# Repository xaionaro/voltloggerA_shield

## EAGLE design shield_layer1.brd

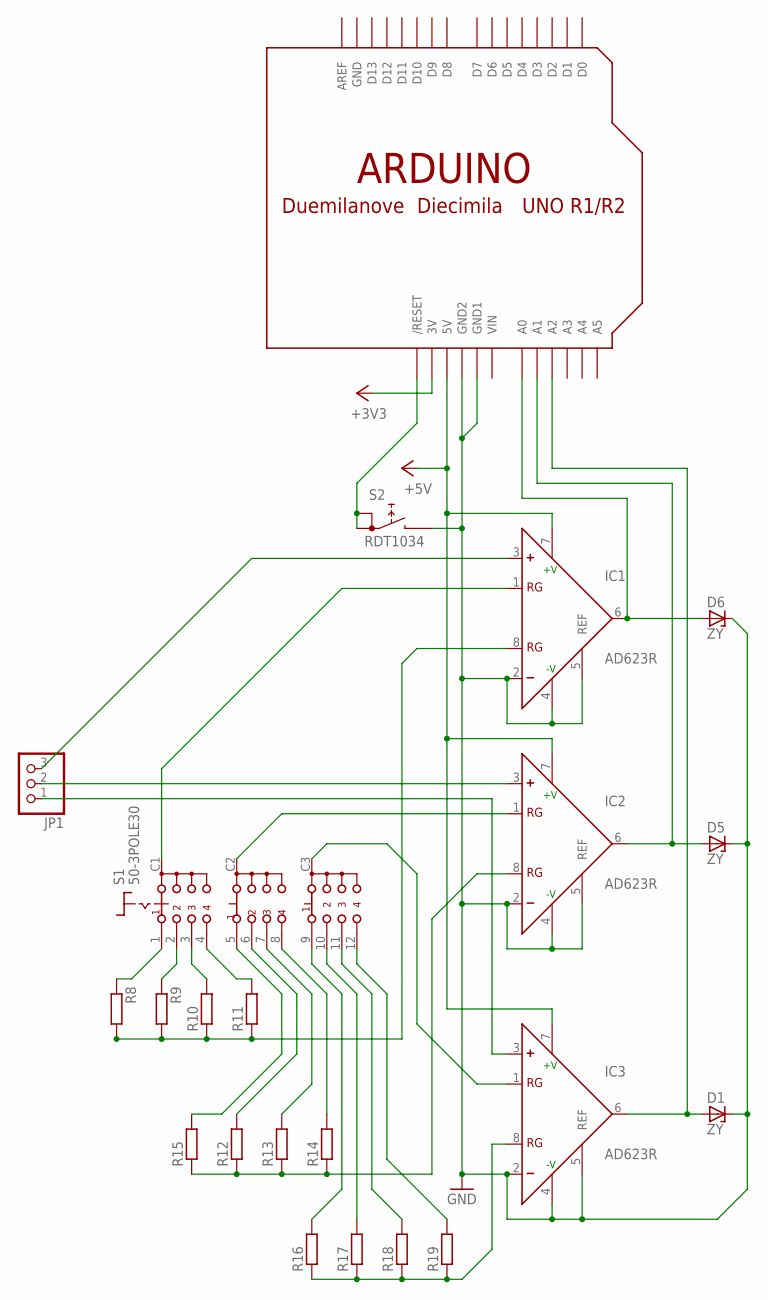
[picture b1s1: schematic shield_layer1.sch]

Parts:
D1, D5, D6: ZY; P1Z12
IC1, IC2, IC3: AD623R; SO8
JP1: PINHD-1X3; 1X03
R8, R9, R10, R11, R12, R13, R14, R15, R16, R17, R18, R19: R-EU_0207/10; 0207/10
S1: 50-3POLE30
S2: RDT1034
U$1: ARDUINOUNO; ARDUINO

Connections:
5V: U$1.3V
+5V: IC1.7 (+V), IC2.7 (+V), IC3.7 (+V), U$1.5V
GND: D1.C, D5.C, D6.C, IC1.2 (-), IC1.4 (-V), IC1.5 (REF), IC2.2 (-), IC2.4 (-V), IC2.5 (REF), IC3.2 (-), IC3.4 (-V), IC3.5 (REF), S2.B, U$1.GND, U$1.GND1, U$1.GND2
unnamed: IC1.1 (RG), S1.C1 (A)
unnamed: IC2.1 (RG), S1.C2 (B)
unnamed: IC2.8 (RG), R12.1, R13.1, R14.1, R15.1
unnamed: IC3.1 (RG), S1.C3 (C)
unnamed: IC3.8 (RG), R16.1, R17.1, R18.1, R19.1
unnamed: D6.A, IC1.6 (OUT), U$1.A0
unnamed: D5.A, IC2.6 (OUT), U$1.A1
unnamed: D1.A, IC3.6 (OUT), U$1.A2
unnamed: R8.1, S1.1 (A1)
unnamed: R9.1, S1.2 (A2)
unnamed: R10.2, S1.3 (A3)
unnamed: S2.A, S2.A1, U$1.RESET (/RESET)
unnamed: R11.2, S1.4 (A4)
unnamed: R15.2, S1.5 (B1)
unnamed: R12.2, S1.6 (B2)
unnamed: R13.2, S1.7 (B3)
unnamed: R14.2, S1.8 (B4)
unnamed: R16.2, S1.9 (C1)
unnamed: R17.2, S1.10 (C2)
unnamed: R18.2, S1.11 (C3)
unnamed: R19.2, S1.12 (C4)
unnamed: IC1.8 (RG), R8.2, R9.2, R10.1, R11.1
unnamed: IC1.3 (+), JP1.3
unnamed: IC3.3 (+), JP1.1
unnamed: IC2.3 (+), JP1.2
VIN: U$1.VIN

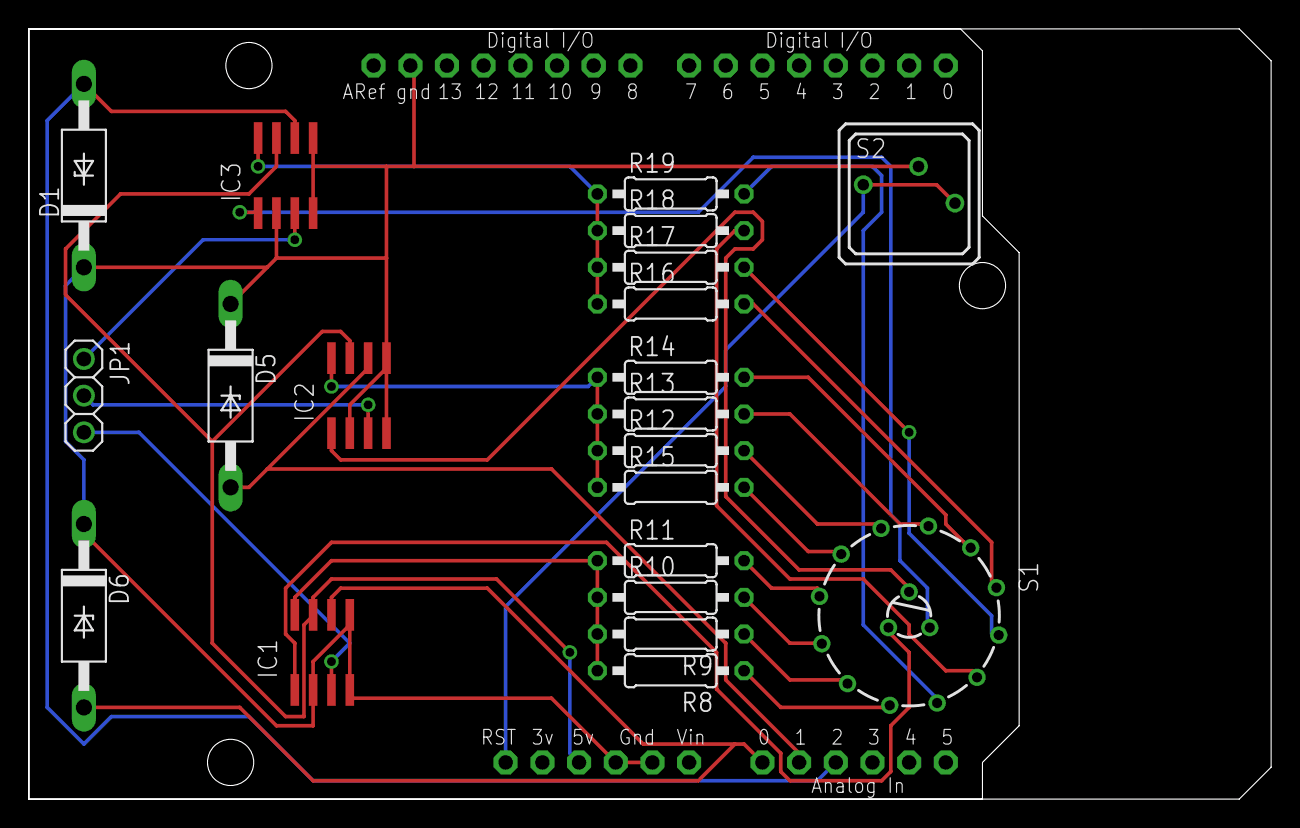
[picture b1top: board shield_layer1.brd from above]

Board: 2 copper layers, 86.0 x 53.3 mm, 22 parts (0 on the bottom side), 27 nets.

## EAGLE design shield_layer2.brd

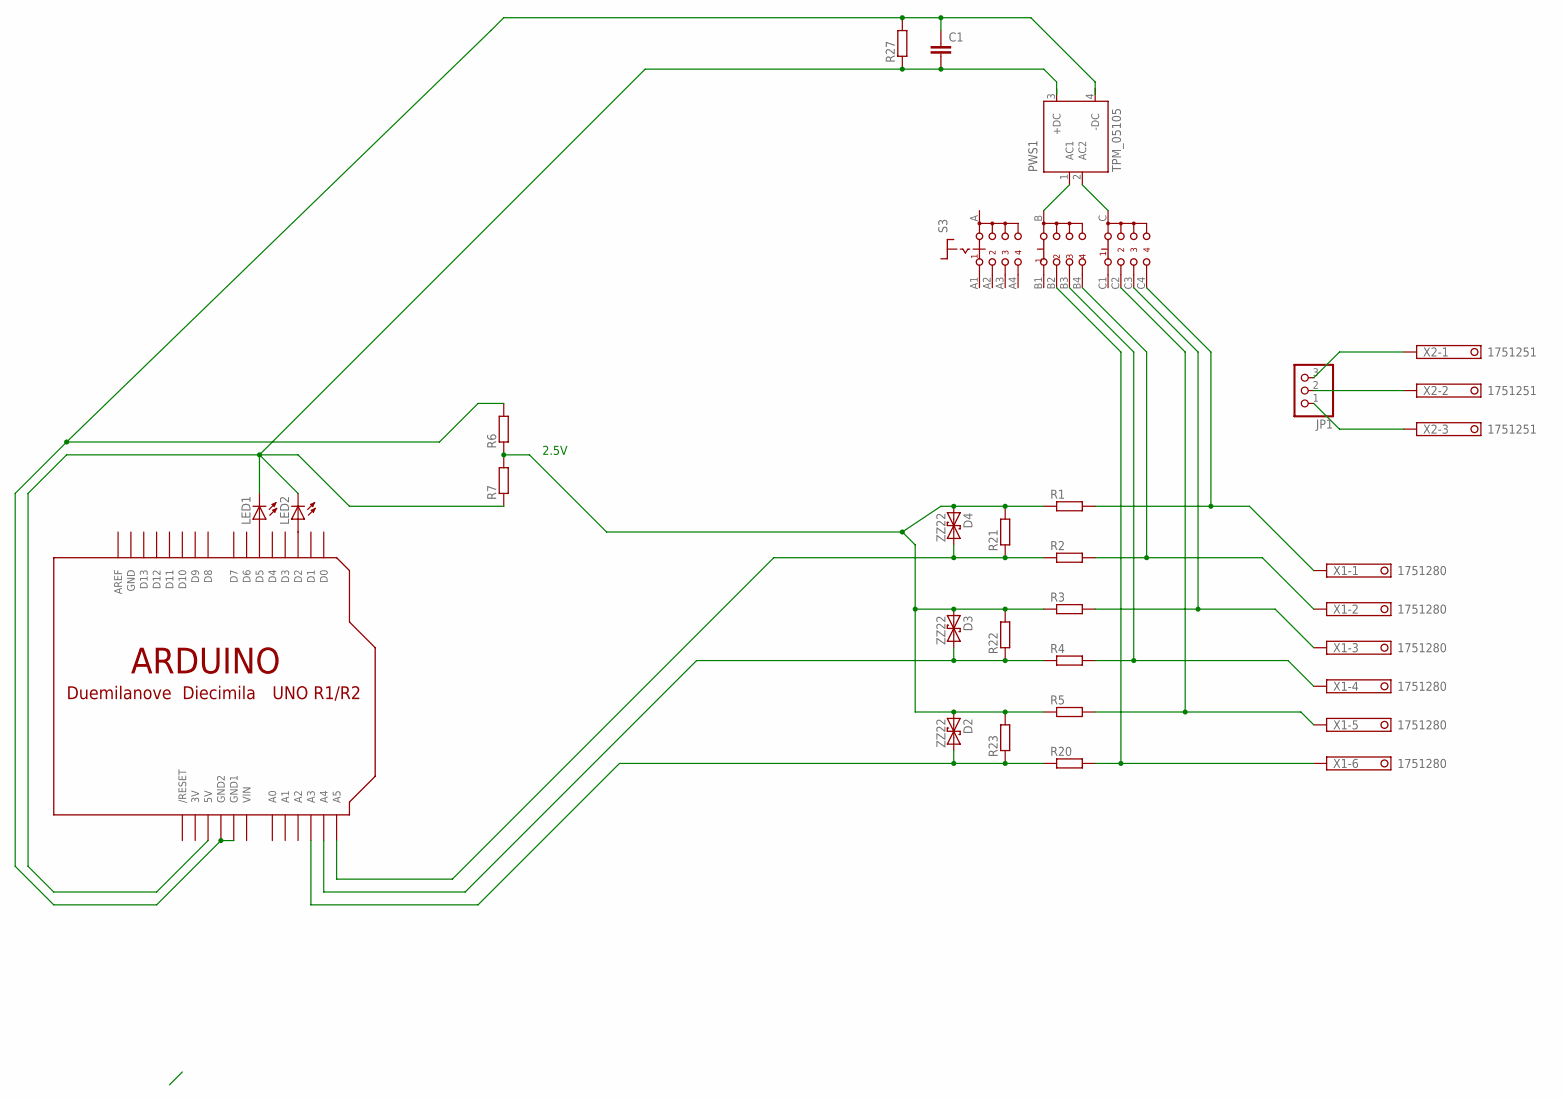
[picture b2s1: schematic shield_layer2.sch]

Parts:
C1: C-EU050-045X075; C050-045X075
D2, D3, D4: ZZ22; P2-15
JP1: PINHD-1X3CB; 1X03-CLEANBIG
LED1, LED2: LED5MM
PWS1: TPM_05105; 05105
R1, R2, R3, R4, R5, R20: R-EU_0617/22; 0617/22
R6, R7, R21, R22, R23, R27: R-EU_0207/10; 0207/10
S3: CK103X04
U$1: ARDUINOUNO; ARDUINO
X1: 1751280
X2: 1751251

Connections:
3V: U$1.3V
GND: U$1.GND
unnamed: C1.2, LED1.K (C), LED2.K (C), R7.1, R27.1, U$1.5V
unnamed: PWS1.1 (AC1), S3.B
unnamed: JP1.3, X2.1
unnamed: JP1.2, X2.2
unnamed: JP1.1, X2.3
unnamed: PWS1.2 (AC2), S3.C
unnamed: D2.C (2), R20.1, R23.1, U$1.A3
unnamed: D3.C (2), R4.1, R22.1, U$1.A4
unnamed: D4.C (2), R2.1, R21.1, U$1.A5
unnamed: C1.1, R6.2, R27.2, U$1.GND1, U$1.GND2
unnamed: LED2.A, U$1.D2
unnamed: LED1.A, U$1.D5
unnamed: R1.2, S3.C4, X1.1
unnamed: R3.2, S3.C3, X1.3
unnamed: D2.A (1), D3.A (1), D4.A (1), R1.1, R3.1, R5.1, R6.1, R7.2, R21.2, R22.2, R23.2
unnamed: R5.2, S3.C2, X1.5
unnamed: R20.2, S3.B2, X1.6
unnamed: R2.2, S3.B4, X1.2
unnamed: R4.2, S3.B3, X1.4
VIN: U$1.VIN

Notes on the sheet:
2.5V

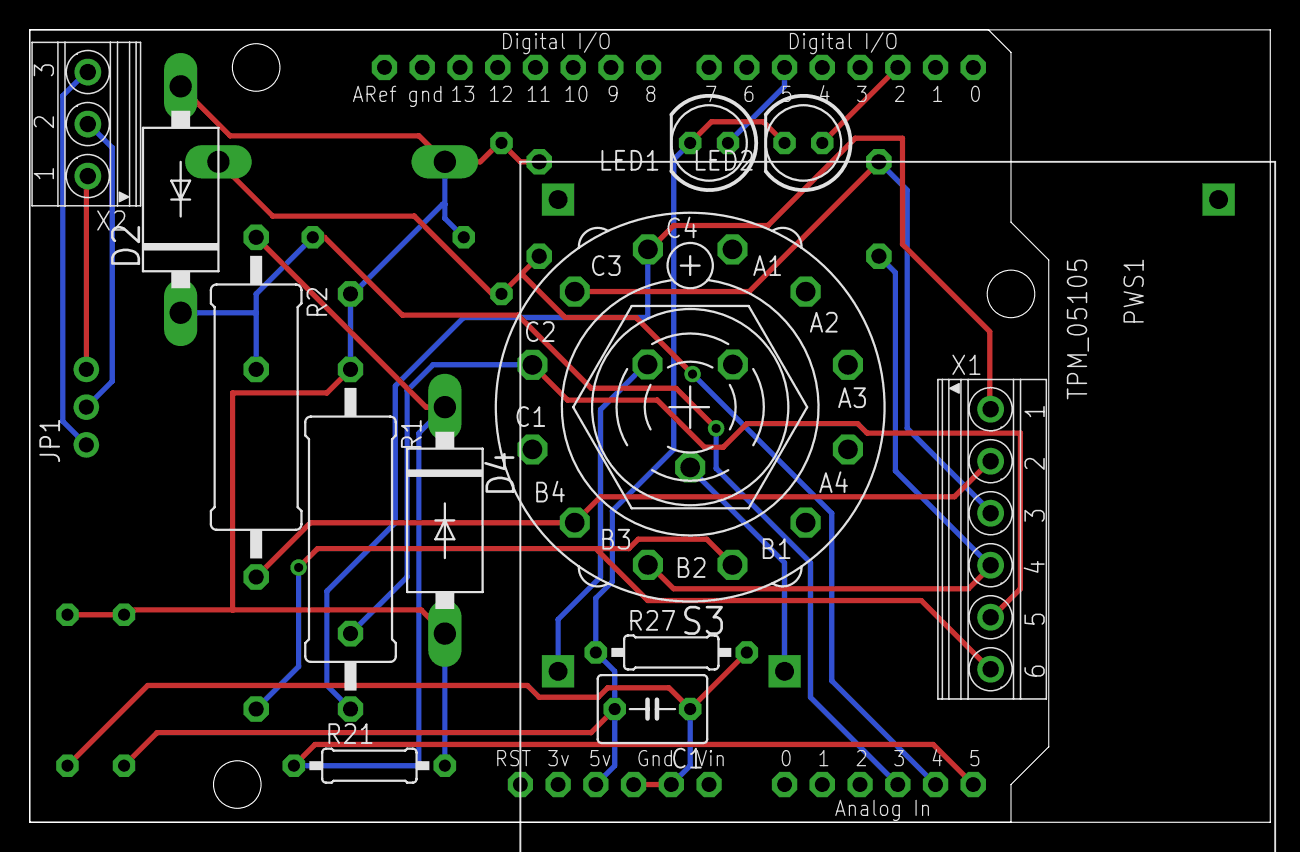
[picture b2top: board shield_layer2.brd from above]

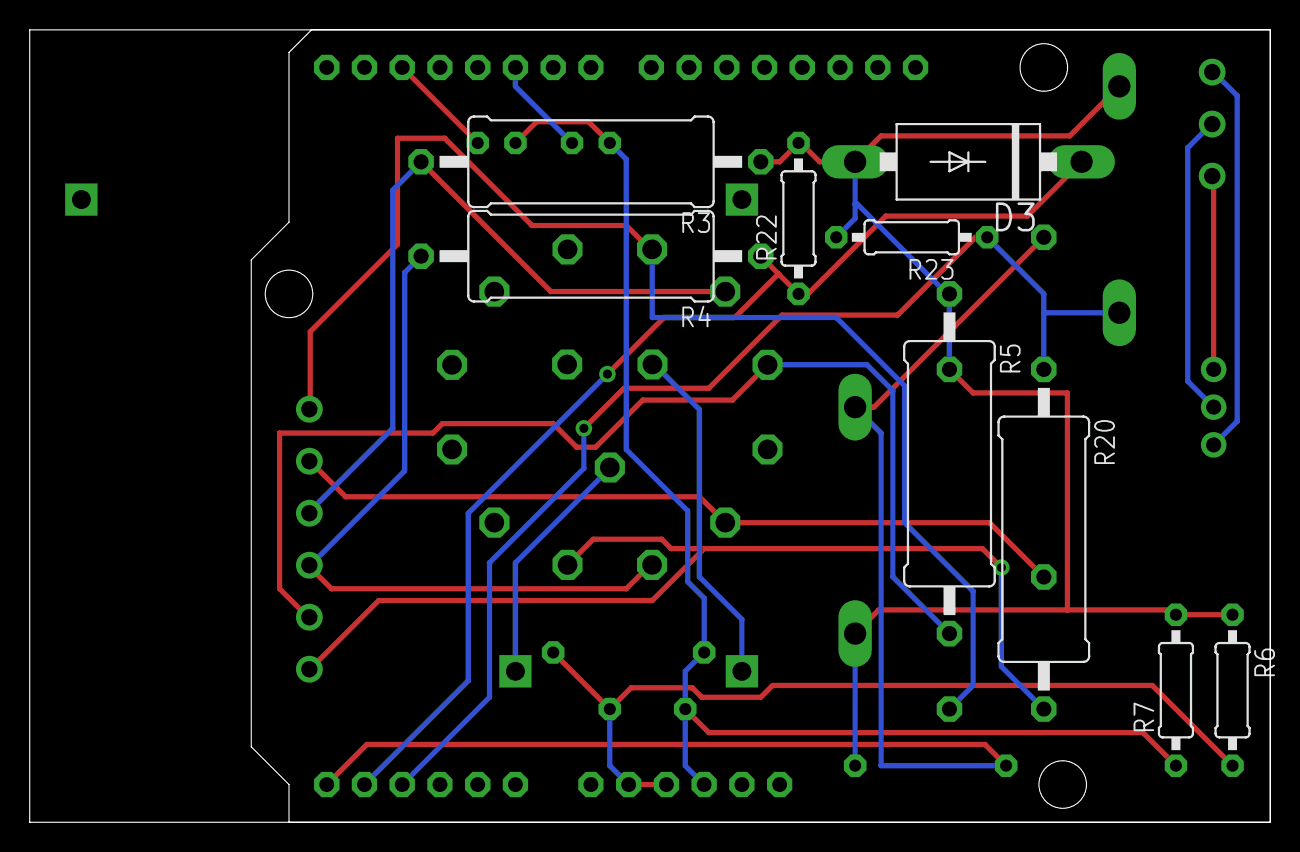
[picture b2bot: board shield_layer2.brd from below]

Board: 2 copper layers, 83.5 x 53.3 mm, 24 parts (9 on the bottom side), 19 nets.

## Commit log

2015-07-29 Added LICENSE file
2015-07-30 Connected A0-A2 amplifiers to signals
2015-07-30 Fixed some errors
2015-07-30 Fixed more errors
2015-07-30 Splitted the board to two
